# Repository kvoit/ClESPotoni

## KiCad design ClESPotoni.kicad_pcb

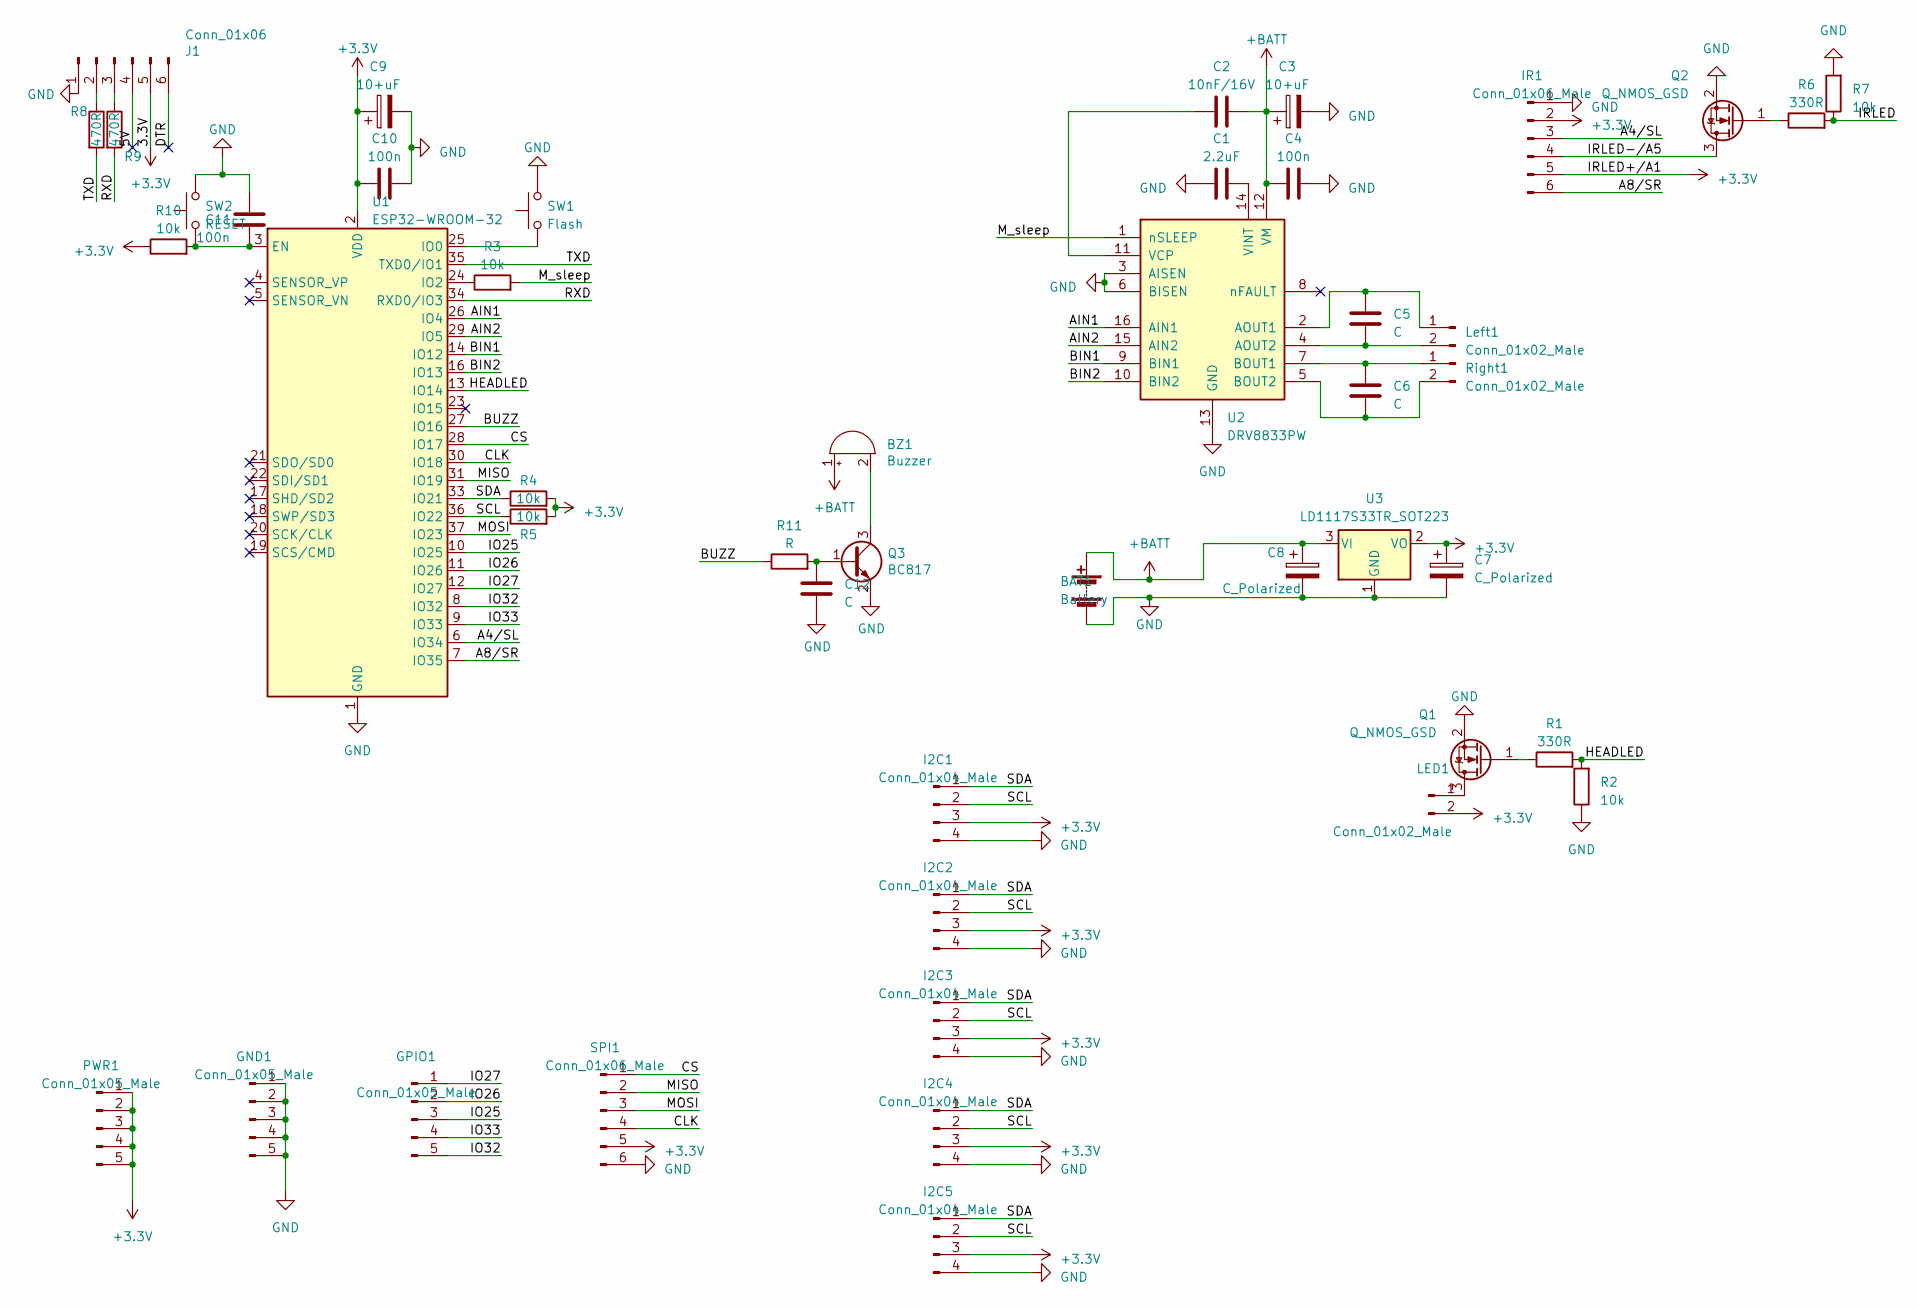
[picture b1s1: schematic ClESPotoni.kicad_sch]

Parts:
BAT1: Battery; JST_EH_B2B-EH-A_1x02_P2.50mm_Vertical
BZ1: Buzzer; Buzzer_12x9.5RM7.6
C1: 2.2uF; C_0603_1608Metric
C2: 10nF/16V; C_0603_1608Metric
C3, C9: 10+uF; CP_EIA-6032-28_Kemet-C
C4, C10, C11: 100n; C_0603_1608Metric
C5, C6, C12: C; C_0603_1608Metric
C7, C8: C_Polarized; CP_EIA-6032-28_Kemet-C
GND1: Conn_01x05_Male; PinHeader_1x05_P2.54mm_Vertical
GPIO1: Conn_01x05_Male; PinHeader_1x05_P2.54mm_Vertical
I2C1, I2C2, I2C3, I2C4, I2C5: Conn_01x04_Male; JST_EH_B4B-EH-A_1x04_P2.50mm_Vertical
IR1: Conn_01x06_Male; JST_PH_B6B-PH-K_1x06_P2.00mm_Vertical
J1: Conn_01x06; PinHeader_1x06_P2.54mm_Vertical
LED1: Conn_01x02_Male; JST_EH_B2B-EH-A_1x02_P2.50mm_Vertical
Left1: Conn_01x02_Male; JST_EH_B2B-EH-A_1x02_P2.50mm_Vertical
PWR1: Conn_01x05_Male; PinHeader_1x05_P2.54mm_Vertical
Q1, Q2: Q_NMOS_GSD; SOT-23
Q3: BC817; SOT-23
R1, R6: 330R; R_0603_1608Metric
R2, R3, R4, R5, R7, R10: 10k; R_0603_1608Metric
R8, R9: 470R; R_0603_1608Metric
R11: R; R_0603_1608Metric
Right1: Conn_01x02_Male; JST_EH_B2B-EH-A_1x02_P2.50mm_Vertical
SPI1: Conn_01x06_Male; JST_EH_B6B-EH-A_1x06_P2.50mm_Vertical
SW1: Flash; SW_SPST_B3S-1000
SW2: RESET; SW_SPST_B3S-1000
U1: ESP32-WROOM-32
U2: DRV8833PW; TSSOP-16_4.4x5mm_P0.65mm
U3: LD1117S33TR_SOT223; SOT-223-3_TabPin2

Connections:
+3.3V: C7.1, C9.1, C10.2, I2C1.3, I2C2.3, I2C3.3, I2C4.3, I2C5.3, IR1.2, IR1.5, J1.5, LED1.2, PWR1.1, PWR1.2, PWR1.3, PWR1.4, PWR1.5, R4.2, R5.2, R10.1, SPI1.5, U1.2 (VDD), U3.2 (VO)
+BATT: BAT1.1 (+), BZ1.1 (-), C2.2, C3.1, C4.2, C8.1, U2.12 (VM), U3.3 (VI)
/5V: J1.4
/A4/SL: IR1.3, U1.6 (IO34)
/A8/SR: IR1.6, U1.7 (IO35)
/AIN1: U1.26 (IO4), U2.16 (AIN1)
/AIN2: U1.29 (IO5), U2.15 (AIN2)
/BIN1: U1.14 (IO12), U2.9 (BIN1)
/BIN2: U1.16 (IO13), U2.10 (BIN2)
/BUZZ: R11.1, U1.27 (IO16)
/CLK: SPI1.4, U1.30 (IO18)
/CS: SPI1.1, U1.28 (IO17)
/DTR: J1.6
/HEADLED: R1.2, R2.2, U1.13 (IO14)
/IO25: GPIO1.3, U1.10 (IO25)
/IO26: GPIO1.2, U1.11 (IO26)
/IO27: GPIO1.1, U1.12 (IO27)
/IO32: GPIO1.5, U1.8 (IO32)
/IO33: GPIO1.4, U1.9 (IO33)
/IRLED: R6.2, R7.1
/IRLED-/A5: IR1.4, Q2.3 (D)
/MISO: SPI1.2, U1.31 (IO19)
/MOSI: SPI1.3, U1.37 (IO23)
/M_sleep: R3.2, U2.1 (nSLEEP)
/RXD: R9.2, U1.34 (RXD0/IO3)
/SCL: I2C1.2, I2C2.2, I2C3.2, I2C4.2, I2C5.2, R5.1, U1.36 (IO22)
/SDA: I2C1.1, I2C2.1, I2C3.1, I2C4.1, I2C5.1, R4.1, U1.33 (IO21)
/TXD: R8.2, U1.35 (TXD0/IO1)
GND: BAT1.2 (-), C1.2, C3.2, C4.1, C7.2, C8.2, C9.2, C10.1, C11.1, C12.2, GND1.1, GND1.2, GND1.3, GND1.4, GND1.5, I2C1.4, I2C2.4, I2C3.4, I2C4.4, I2C5.4, IR1.1, J1.1, Q1.2 (S), Q2.2 (S), Q3.2 (E), R2.1, R7.2, SPI1.6, SW1.2, SW2.2, U1.1 (GND), U1.15 (GND), U1.38 (GND), U1.39 (GND), U2.3 (AISEN), U2.6 (BISEN), U2.13 (GND), U3.1 (GND)
unnamed: BZ1.2 (+), Q3.3 (C)
unnamed: J1.2, R8.1
unnamed: J1.3, R9.1
unnamed: LED1.1, Q1.3 (D)
unnamed: C5.1, Left1.1, U2.2 (AOUT1)
unnamed: C5.2, Left1.2, U2.4 (AOUT2)
unnamed: Q1.1 (G), R1.1
unnamed: Q2.1 (G), R6.1
unnamed: C12.1, Q3.1 (B), R11.2
unnamed: C6.1, Right1.1, U2.7 (BOUT1)
unnamed: C6.2, Right1.2, U2.5 (BOUT2)
unnamed: C11.2, R10.2, SW2.1, U1.3 (EN)
unnamed: SW1.1, U1.25 (IO0)
unnamed: R3.1, U1.24 (IO2)
unnamed: C2.1, U2.11 (VCP)
unnamed: C1.1, U2.14 (VINT)

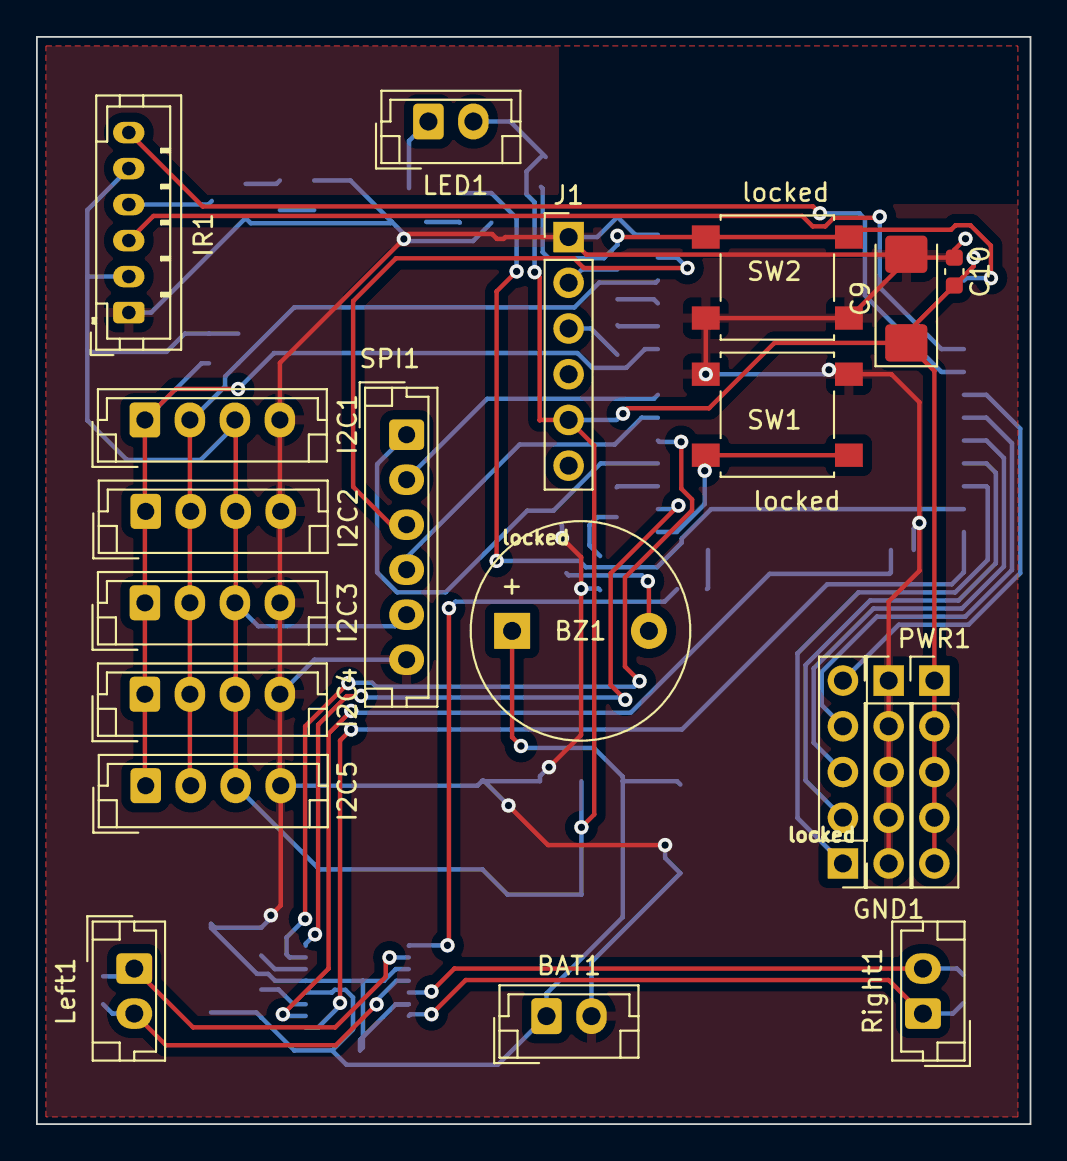
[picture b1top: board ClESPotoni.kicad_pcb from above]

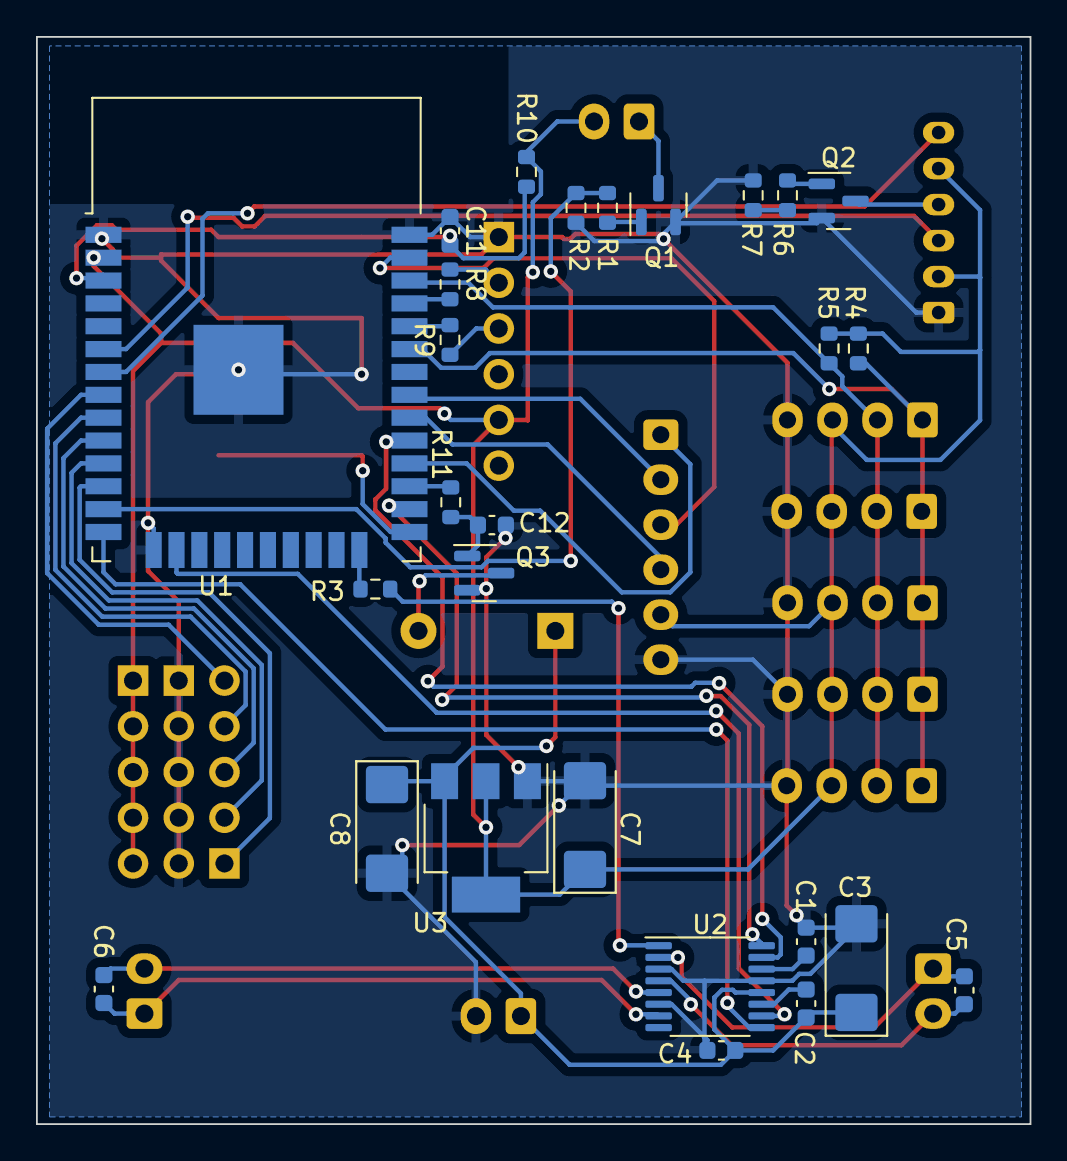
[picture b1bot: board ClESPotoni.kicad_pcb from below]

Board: 2 copper layers, 55.2 x 60.4 mm, 47 parts (27 on the bottom side), 43 nets.

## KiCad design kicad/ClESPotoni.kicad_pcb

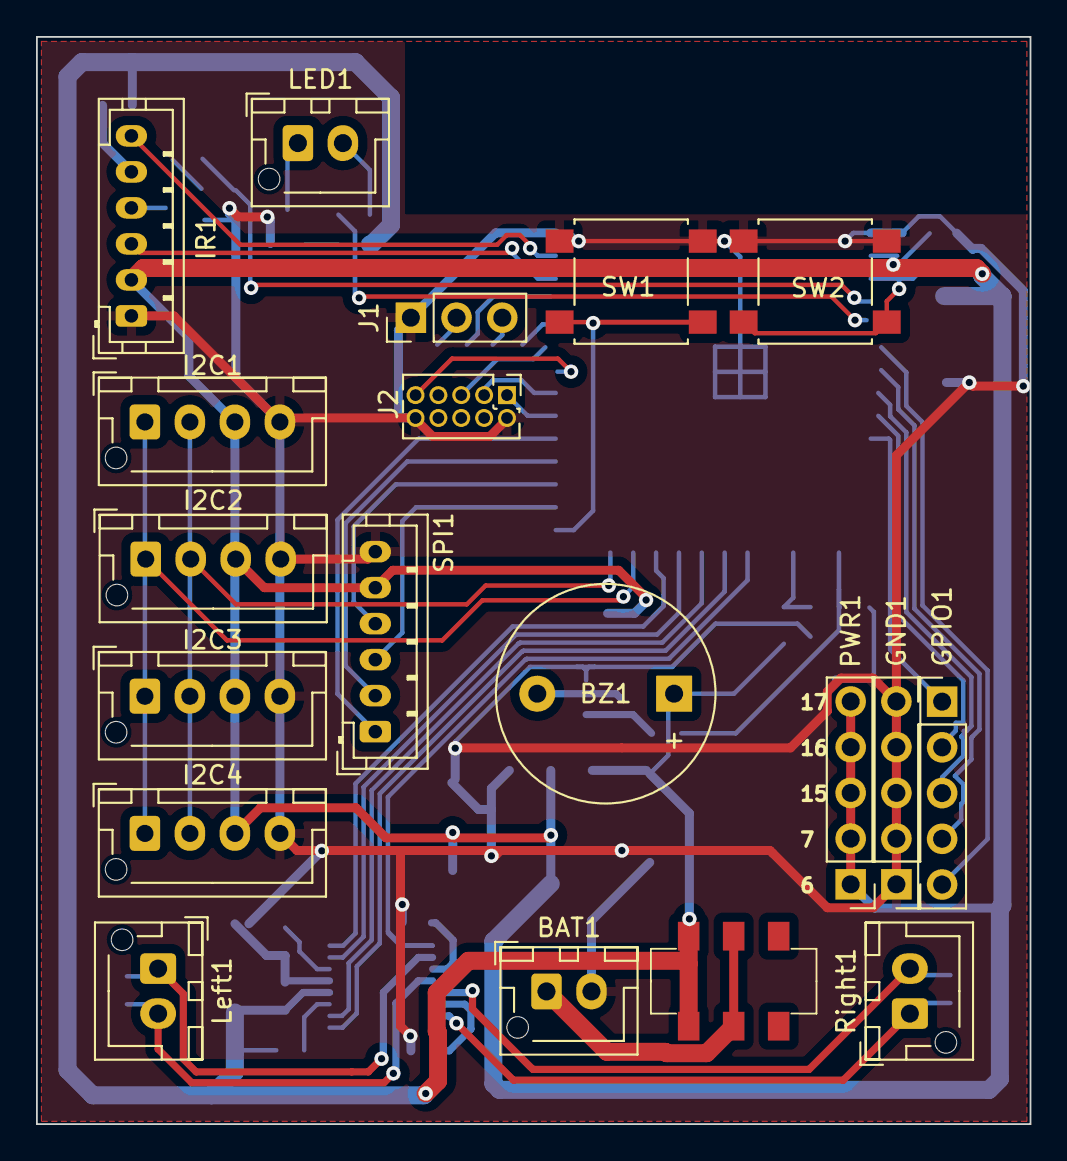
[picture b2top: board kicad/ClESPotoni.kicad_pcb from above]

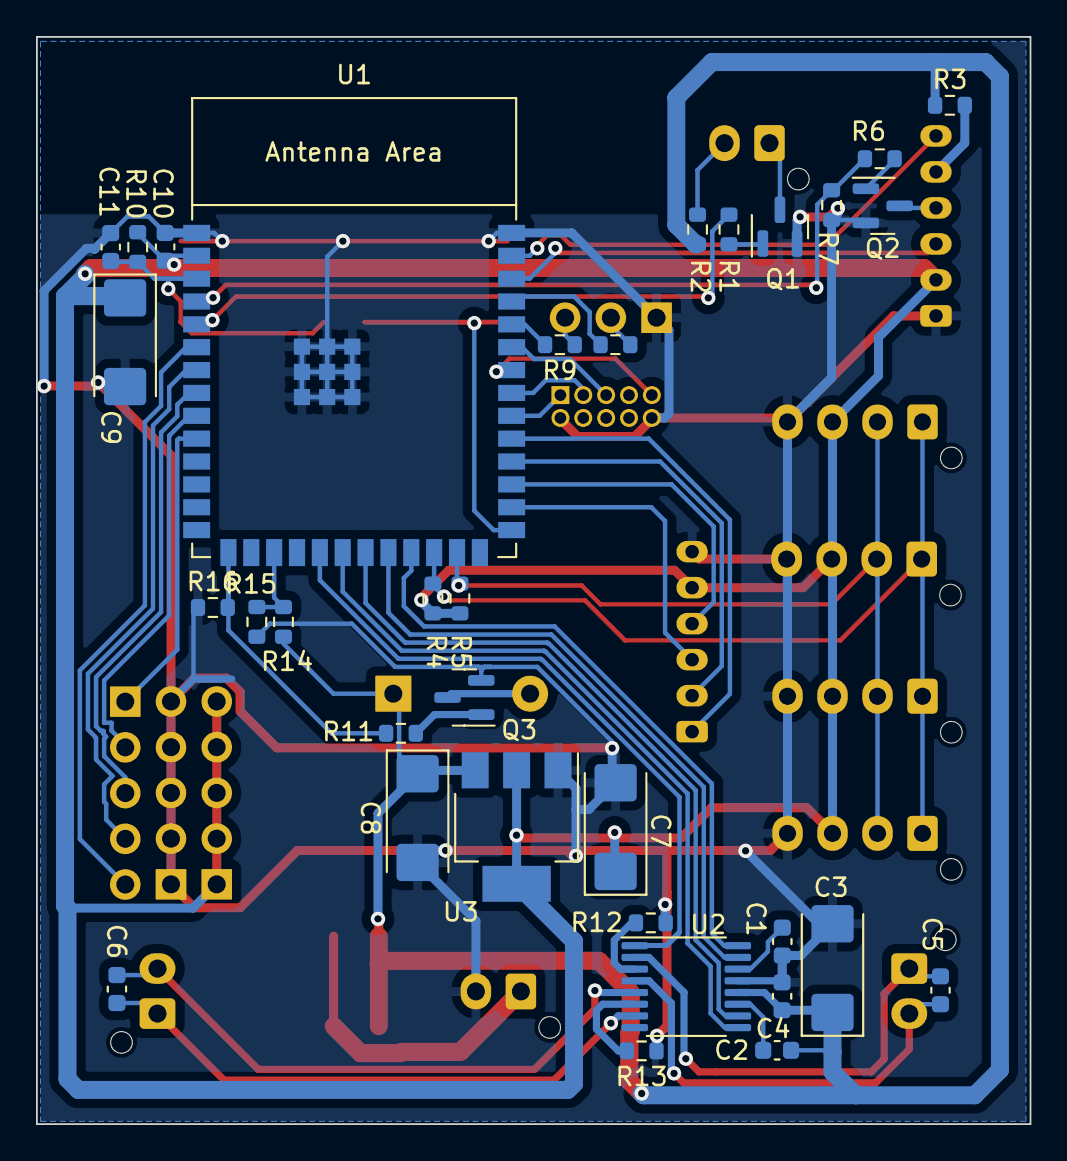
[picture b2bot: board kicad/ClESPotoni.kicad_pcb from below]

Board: 2 copper layers, 55.2 x 60.4 mm, 52 parts (33 on the bottom side), 52 nets.

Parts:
BAT1: Battery; JST_XH_B2B-XH-AM_1x02_P2.50mm_Vertical
BZ1: Buzzer; Buzzer_12x9.5RM7.6
C1: 2.2uF; C_0603_1608Metric
C2: 10nF/16V; C_0603_1608Metric
C3, C9: 10+uF; CP_EIA-6032-28_Kemet-C
C4, C10: 100n; C_0603_1608Metric
C5, C6: C; C_0603_1608Metric
C7, C8: 10u; CP_EIA-6032-28_Kemet-C
C11: 1u; C_0603_1608Metric
GND1: Conn_01x04_Male; PinHeader_1x05_P2.54mm_Vertical
GPIO1: Conn_01x04_Male; PinHeader_1x05_P2.54mm_Vertical
I2C1, I2C2, I2C3, I2C4: Conn_01x04_Male; JST_XH_B4B-XH-AM_1x04_P2.50mm_Vertical
IR1: Conn_01x06_Male; JST_PH_B6B-PH-K_1x06_P2.00mm_Vertical
J1: Conn_01x06; PinHeader_1x03_P2.54mm_Vertical
J2: AVR-JTAG-10; PinHeader_2x05_P1.27mm_Vertical
LED1: Conn_01x02_Male; JST_XH_B2B-XH-AM_1x02_P2.50mm_Vertical
Left1: Conn_01x02_Male; JST_XH_B2B-XH-AM_1x02_P2.50mm_Vertical
PWR1: Conn_01x04_Male; PinHeader_1x05_P2.54mm_Vertical
Q1, Q2: Q_NMOS_GSD; SOT-23
Q3: BC817; SOT-23
R1, R2, R6: 330R; R_0603_1608Metric
R3: ?R; R_0603_1608Metric
R4, R5, R7, R10, R15: 10k; R_0603_1608Metric
R8, R9: 470R; R_0603_1608Metric
R11: 330; R_0603_1608Metric
R12, R13: 0.2R; R_0603_1608Metric
R14, R16: 10K; R_0603_1608Metric
Right1: Conn_01x02_Male; JST_XH_B2B-XH-AM_1x02_P2.50mm_Vertical
SPI1: Conn_01x06_Male; JST_PH_B6B-PH-K_1x06_P2.00mm_Vertical
SW1: Flash; SW_SPST_B3S-1000
SW2: RESET; SW_SPST_B3S-1000
SW3: SW_DPDT_x2; Switch_DPDT
U1: ESP32-S3-WROOM-1
U2: DRV8833PW; TSSOP-16_4.4x5mm_P0.65mm
U3: LD1117S33TR_SOT223; SOT-223-3_TabPin2

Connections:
+3.3V: C7.1, C9.1, C10.2, I2C1.3, I2C2.3, I2C3.3, I2C4.3, IR1.2, PWR1.1, PWR1.2, PWR1.3, PWR1.4, PWR1.5, R4.2, R5.2, R10.1, SPI1.5, U1.2 (3V3), U3.2 (VO)
+BATT: BZ1.1 (-), C2.2, C3.1, C4.2, C8.1, R2.1, R3.1, R15.1, SW3.1 (A), SW3.4 (A), U2.12 (VM), U3.3 (VI)
/A4/SL: IR1.3, U1.38 (GPIO2/TOUCH2/ADC1_CH1)
/A8/SR: IR1.6, U1.39 (GPIO1/TOUCH1/ADC1_CH0)
/AIN1: U1.23 (GPIO21), U2.16 (AIN1)
/AIN2: U1.22 (GPIO14/TOUCH14/ADC2_CH3/FSPIWP/FSPIDQS/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), U2.15 (AIN2)
/BAT_SENSE: R14.1, R15.2, U1.17 (GPIO9/TOUCH9/ADC1_CH8/FSPIHD/SUBSPIHD)
/BIN1: U1.20 (GPIO12/TOUCH12/ADC2_CH1/FSPICLK/FSPIIO6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), U2.9 (BIN1)
/BIN2: U1.21 (GPIO13/TOUCH13/ADC2_CH2/FSPIQ/FSPIIO7/S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), U2.10 (BIN2)
/BOOT: SW1.1, U1.27 (GPIO0/BOOT)
/BUZZ: R11.1, R16.2, U1.15 (GPIO3/TOUCH3/ADC1_CH2)
/CLK: SPI1.4, U1.29 (SPIIO7/GPIO36/FSPICLK/SUBSPICLK)
/CS: SPI1.1, U1.31 (GPIO38/FSPIWP/SUBSPIWP)
/HEADLED: R1.2, U1.5 (GPIO5/TOUCH5/ADC1_CH4)
/IO06: GPIO1.5, U1.6 (GPIO6/TOUCH6/ADC1_CH5)
/IO07: GPIO1.4, U1.7 (GPIO7/TOUCH7/ADC1_CH6)
/IO15: GPIO1.3, U1.8 (GPIO15/U0RTS/ADC2_CH4/XTAL_32K_P)
/IO16: GPIO1.2, U1.9 (GPIO16/U0CTS/ADC2_CH5/XTAL_32K_N)
/IO17: GPIO1.1, U1.10 (GPIO17/U1TXD/ADC2_CH6)
/IRLED: R6.2, R7.1, U1.4 (GPIO4/TOUCH4/ADC1_CH3)
/IRLED+/A1: IR1.5, R3.2
/IRLED-/A5: IR1.4, Q2.3 (D)
/MISO: SPI1.2, U1.30 (SPIDQS/GPIO37/FSPIQ/SUBSPIQ)
/MOSI: SPI1.3, U1.28 (SPIIO6/GPIO35/FSPID/SUBSPID)
/M_sleep: U1.19 (GPIO11/TOUCH11/ADC2_CH0/FSPID/FSPIIO5/S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), U2.1 (nSLEEP)
/RXD: R9.2, U1.36 (U0RXD/GPIO44/CLK_OUT2)
/SCL: I2C1.2, I2C2.2, I2C3.2, I2C4.2, R5.1, U1.25 (GPIO48/SPICLK_N/SUBSPICLK_N_DIFF)
/SDA: I2C1.1, I2C2.1, I2C3.1, I2C4.1, R4.1, U1.24 (GPIO47/SPICLK_P/SUBSPICLK_P_DIFF)
/TCK: J2.1 (TCK), U1.32 (MTCK/GPIO39/CLK_OUT3/SUBSPICS1)
/TDI: J2.9 (TDI), U1.34 (MTDI/GPIO41/CLK_OUT1)
/TDO: J2.3 (TDO), U1.33 (MTDO/GPIO40/CLK_OUT2)
/TMS: J2.5 (TMS), U1.35 (MTMS/GPIO42)
/TXD: R8.2, U1.37 (U0TXD/GPIO43/CLK_OUT1)
GND: BAT1.2 (-), C1.2, C3.2, C4.1, C7.2, C8.2, C9.2, C10.1, C11.1, GND1.1, GND1.2, GND1.3, GND1.4, GND1.5, I2C1.4, I2C2.4, I2C3.4, I2C4.4, IR1.1, J1.1, J2.2 (GND), J2.10 (GND), Q1.2 (S), Q2.2 (S), Q3.2 (E), R7.2, R12.1, R13.1, R14.2, R16.1, SPI1.6, SW1.2, SW2.2, U1.1 (GND), U1.40 (GND), U1.41 (GND), U2.13 (GND), U3.1 (GND)
unnamed: BAT1.1 (+), SW3.2 (B), SW3.5 (B)
unnamed: BZ1.2 (+), Q3.3 (C)
unnamed: J1.2, R8.1
unnamed: J1.3, R9.1
unnamed: LED1.1, Q1.3 (D)
unnamed: LED1.2, R2.2
unnamed: C5.1, Left1.1, U2.2 (AOUT1)
unnamed: C5.2, Left1.2, U2.4 (AOUT2)
unnamed: Q1.1 (G), R1.1
unnamed: Q2.1 (G), R6.1
unnamed: Q3.1 (B), R11.2
unnamed: C6.1, Right1.1, U2.7 (BOUT1)
unnamed: C6.2, Right1.2, U2.5 (BOUT2)
unnamed: C11.2, R10.2, SW2.1, U1.3 (EN)
unnamed: R12.2, U2.3 (AISEN)
unnamed: R13.2, U2.6 (BISEN)
unnamed: C2.1, U2.11 (VCP)
unnamed: C1.1, U2.14 (VINT)

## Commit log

2023-02-26 v1.0 version
2023-04-16 New version for ESP32-S3-WROOM-1, with bugfixes
2023-04-16 Restructure
2023-04-16 Added simple web control software
